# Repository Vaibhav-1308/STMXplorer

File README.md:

# STMXplorer
An STM32 Based Programming Board.

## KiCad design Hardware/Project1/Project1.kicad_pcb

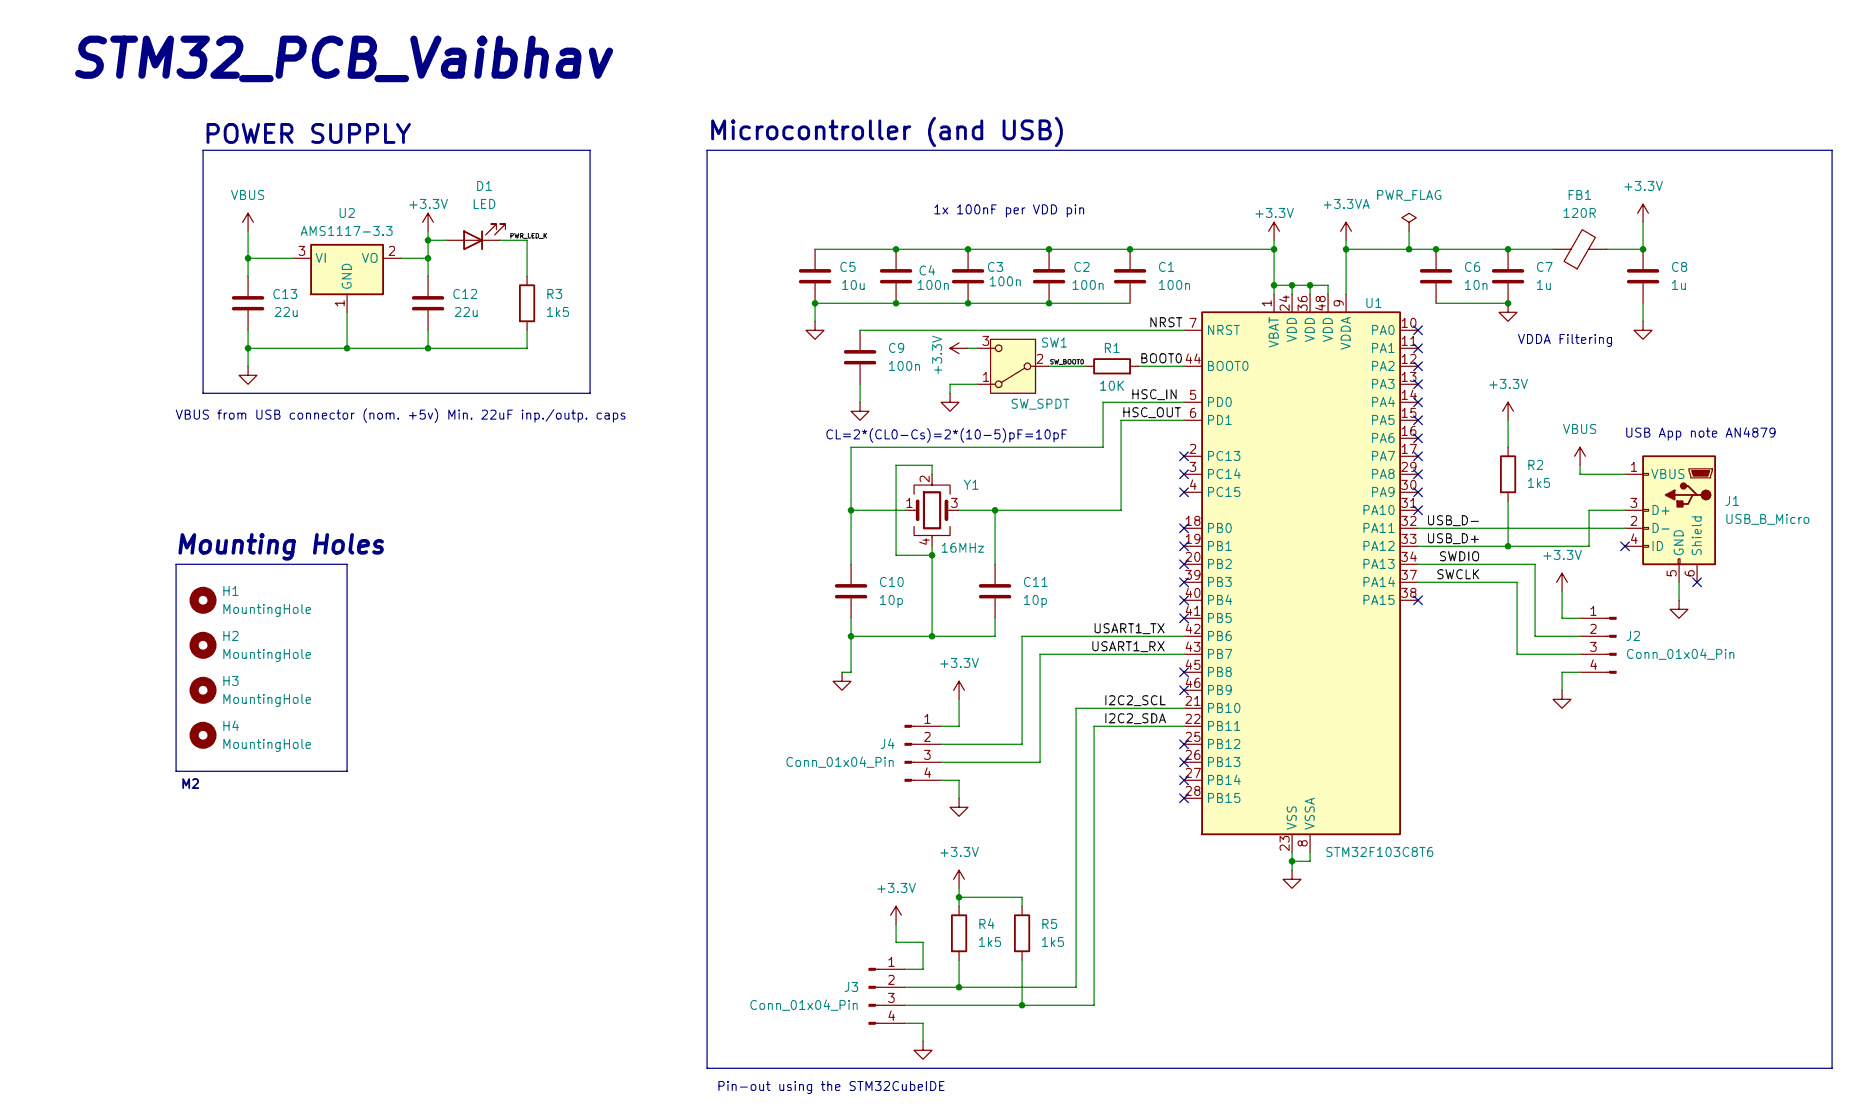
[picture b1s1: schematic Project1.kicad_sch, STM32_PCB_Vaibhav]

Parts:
C1, C2, C3, C4, C9: 100n; C_0402_1005Metric
C5: 10u; C_0603_1608Metric
C6: 10n; C_0402_1005Metric
C7, C8: 1u; C_0402_1005Metric
C10, C11: 10p; C_0402_1005Metric
C12, C13: 22u; C_0805_2012Metric
D1: LED; LED_0603_1608Metric
FB1: 120R; L_0603_1608Metric
H1, H2, H3, H4: MountingHole; MountingHole_2.2mm_M2
J1: USB_B_Micro; USB_Micro-B_Wuerth_629105150521
J2, J3, J4: Conn_01x04_Pin; PinHeader_1x04_P2.54mm_Vertical
R1: 10K; R_0402_1005Metric
R2, R3, R4, R5: 1k5; R_0402_1005Metric
SW1: SW_SPDT; SW_SPDT_PCM12
U1: STM32F103C8T6; LQFP-48_7x7mm_P0.5mm
U2: AMS1117-3.3; SOT-223-3_TabPin2
Y1: 16MHz; Crystal_SMD_3225-4Pin_3.2x2.5mm

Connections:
+3.3V: C1.1, C2.1, C3.1, C4.1, C5.1, C8.1, C12.1, D1.2 (A), FB1.2, J2.1, J3.1, J4.1, R2.1, R4.1, R5.1, SW1.3 (C), U1.1 (VBAT), U1.24 (VDD), U1.36 (VDD), U1.48 (VDD), U2.2 (VO)
+3.3VA: C6.1, C7.1, FB1.1, U1.9 (VDDA)
/BOOT0: R1.2, U1.44 (BOOT0)
/HSC_IN: C10.1, U1.5 (PD0), Y1.1
/HSC_OUT: C11.1, U1.6 (PD1), Y1.3
/I2C2_SCL: J3.2, R4.2, U1.21 (PB10)
/I2C2_SDA: J3.3, R5.2, U1.22 (PB11)
/NRST: C9.1, U1.7 (NRST)
/PWR_LED_K: D1.1 (K), R3.1
/SWCLK: J2.3, U1.37 (PA14)
/SWDIO: J2.2, U1.34 (PA13)
/SW_BOOT0: R1.1, SW1.2 (B)
/USART1_RX: J4.3, U1.43 (PB7)
/USART1_TX: J4.2, U1.42 (PB6)
/USB_D+: J1.3 (D+), R2.2, U1.33 (PA12)
/USB_D-: J1.2 (D-), U1.32 (PA11)
GND: C1.2, C2.2, C3.2, C4.2, C5.2, C6.2, C7.2, C8.2, C9.2, C10.2, C11.2, C12.2, C13.2, J1.5 (GND), J2.4, J3.4, J4.4, R3.2, SW1.1 (A), U1.8 (VSSA), U1.23 (VSS), U1.35 (VSS), U1.47 (VSS), U2.1 (GND), Y1.2, Y1.4
VBUS: C13.1, J1.1 (VBUS), U2.3 (VI)

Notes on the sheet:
Microcontroller (and USB)
CL=2*(CL0-Cs)=2*(10-5)pF=10pF
Pin-out using the STM32CubeIDE
POWER SUPPLY
STM32_PCB_Vaibhav
VDDA Filtering
VBUS from USB connector (nom. +5v) Min. 22uF inp./outp. caps
1x 100nF per VDD pin
Mounting Holes
USB App note AN4879

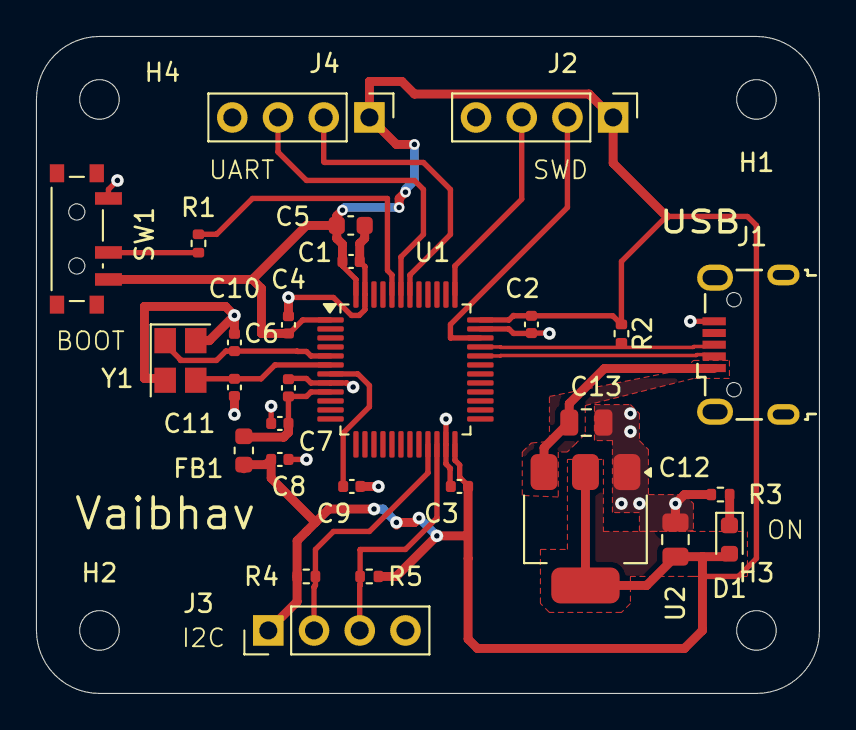
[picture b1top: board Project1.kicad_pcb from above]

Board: 2 copper layers, 43.5 x 36.5 mm, 32 parts (0 on the bottom side), 18 nets.

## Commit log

2024-09-23 Made the STM32 based Project and added the images of PCB
2024-09-23 Update README.md
    Added the image.
